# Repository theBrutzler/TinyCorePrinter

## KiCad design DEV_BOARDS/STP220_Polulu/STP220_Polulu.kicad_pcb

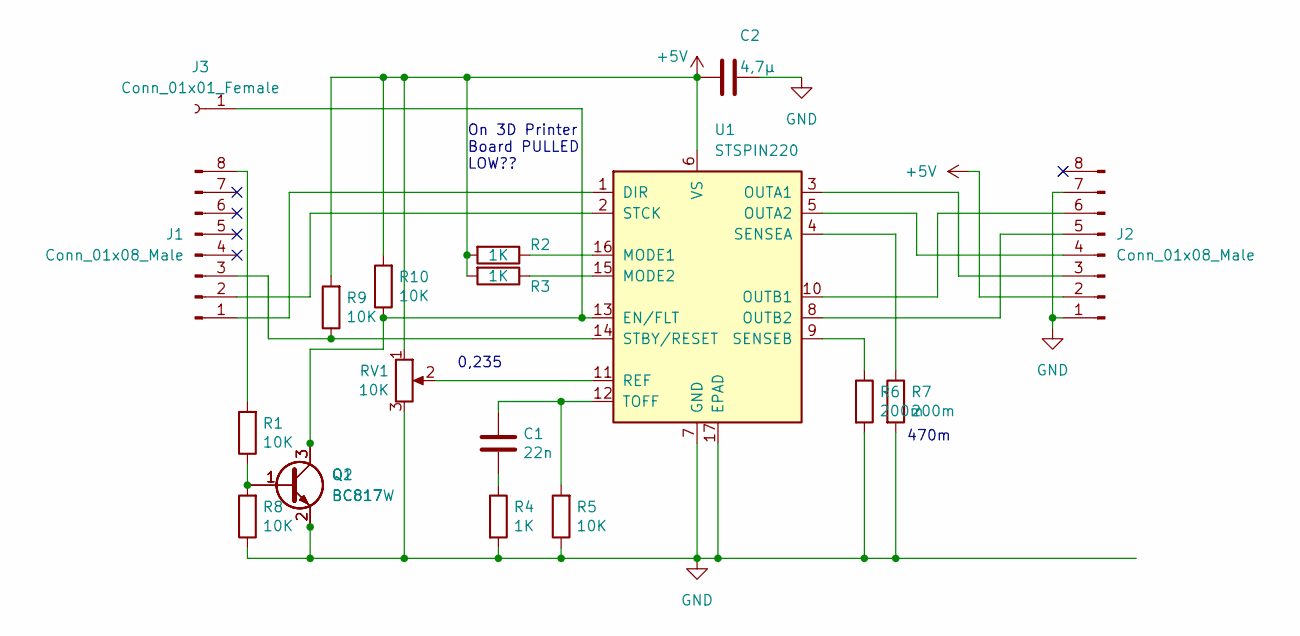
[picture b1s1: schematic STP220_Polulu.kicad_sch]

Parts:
C1: 22n; C_0603_1608Metric
C2: 4,7µ; C_0603_1608Metric
J1, J2: Conn_01x08_Male; PinHeader_1x08_P2.54mm_Vertical
J3: Conn_01x01_Female; TestPoint_Pad_2.0x2.0mm
Q1: BC817; SOT-23
Q2: BC817W; SOT-323_SC-70
R1, R5, R8, R9, R10: 10K; R_0603_1608Metric
R2, R3, R4: 1K; R_0603_1608Metric
R6, R7: 200m; R_0603_1608Metric
RV1: 10K; Potentiometer_Bourns_TC33X_Vertical
U1: STSPIN220; VQFN-16-1EP_3x3mm_P0.5mm_EP1.8x1.8mm

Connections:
+5V: C2.2, J2.2, R2.2, R3.2, R9.2, R10.2, RV1.1, U1.6 (VS)
GND: C2.1, J2.1, J2.7, Q1.2 (E), Q2.2 (E), R4.2, R5.1, R6.2, R7.2, R8.1, RV1.3, U1.7 (GND), U1.17 (EPAD)
unnamed: C1.1, R5.2, U1.12 (TOFF)
unnamed: C1.2, R4.1
unnamed: J1.1, U1.1 (DIR)
unnamed: J1.2, U1.2 (STCK)
unnamed: J1.8, R1.2
unnamed: J3.1, Q1.3 (C), Q2.3 (C), R10.1, U1.13 (EN/FLT)
unnamed: Q1.1 (B), Q2.1 (B), R1.1, R8.2
unnamed: R2.1, U1.16 (MODE1)
unnamed: R3.1, U1.15 (MODE2)
unnamed: R6.1, U1.9 (SENSEB)
unnamed: R7.1, U1.4 (SENSEA)
unnamed: RV1.2, U1.11 (REF)
unnamed: J2.3, U1.3 (OUTA1)
unnamed: J2.4, U1.5 (OUTA2)
unnamed: J2.5, U1.8 (OUTB2)
unnamed: J2.6, U1.10 (OUTB1)
unnamed: J1.3, R9.1, U1.14 (STBY/RESET)

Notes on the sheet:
0,235
On 3D Printer Board PULLED LOW??
470m

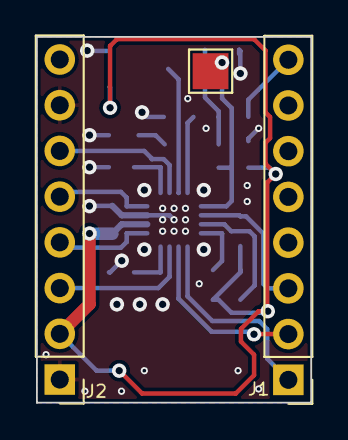
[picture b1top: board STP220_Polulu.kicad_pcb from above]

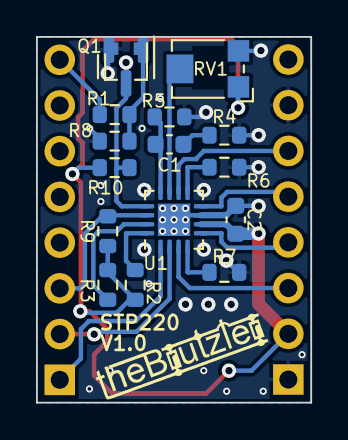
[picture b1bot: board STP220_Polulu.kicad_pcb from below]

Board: 2 copper layers, 15.2 x 20.3 mm, 19 parts (16 on the bottom side), 19 nets.

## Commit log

2025-01-02 initial upload of stp220 polulu shield (UNTESTED)
2025-02-13 update_3d_models and 3d_render
